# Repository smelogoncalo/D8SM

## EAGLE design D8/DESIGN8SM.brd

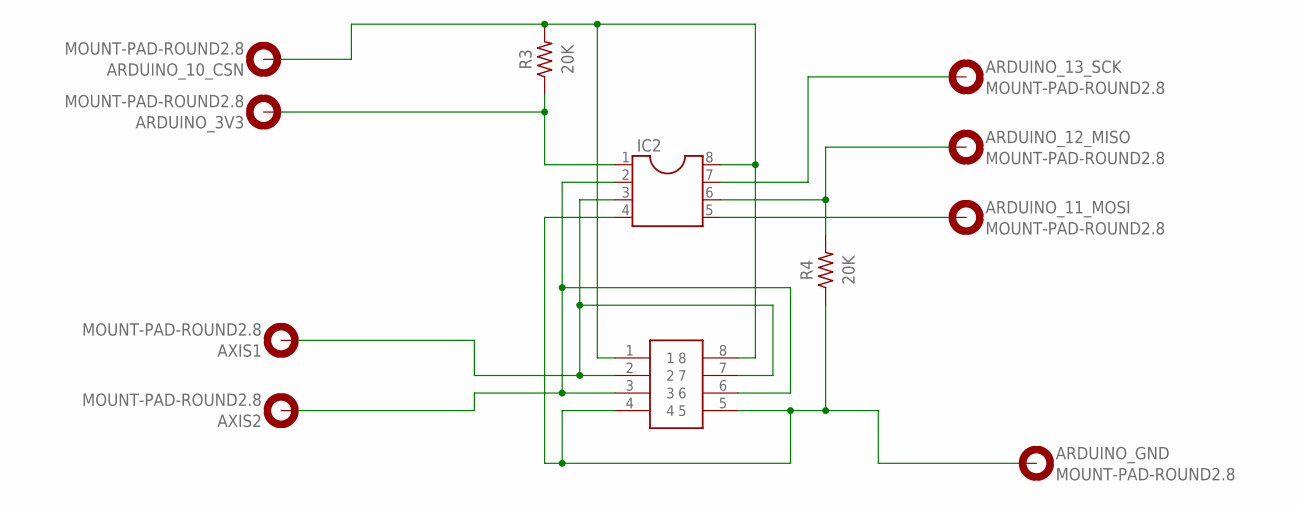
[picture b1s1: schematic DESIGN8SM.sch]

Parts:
ARDUINO_3V3, ARDUINO_10_CSN, ARDUINO_11_MOSI, ARDUINO_12_MISO, ARDUINO_13_SCK: MOUNT-PAD-ROUND2.8; 2,8-PAD
ARDUINO_GND: MOUNT-PAD-ROUND2.8; 2,8-PAD
AXIS1, AXIS2: MOUNT-PAD-ROUND2.8; 2,8-PAD
IC2: DIL8S; SOCKET-08
R3, R4: 20K; RESAD1176W63L850D250B
U$2: JOYSTICK

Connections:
unnamed: ARDUINO_GND.B2,8, IC2.4, R4.1, U$2.4, U$2.5
unnamed: AXIS1.B2,8, IC2.3, U$2.2, U$2.7
unnamed: AXIS2.B2,8, IC2.2, U$2.3, U$2.6
unnamed: ARDUINO_10_CSN.B2,8, IC2.8, R3.2, U$2.1, U$2.8
unnamed: ARDUINO_3V3.B2,8, IC2.1, R3.1
unnamed: ARDUINO_11_MOSI.B2,8, IC2.5
unnamed: ARDUINO_12_MISO.B2,8, IC2.6, R4.2
unnamed: ARDUINO_13_SCK.B2,8, IC2.7

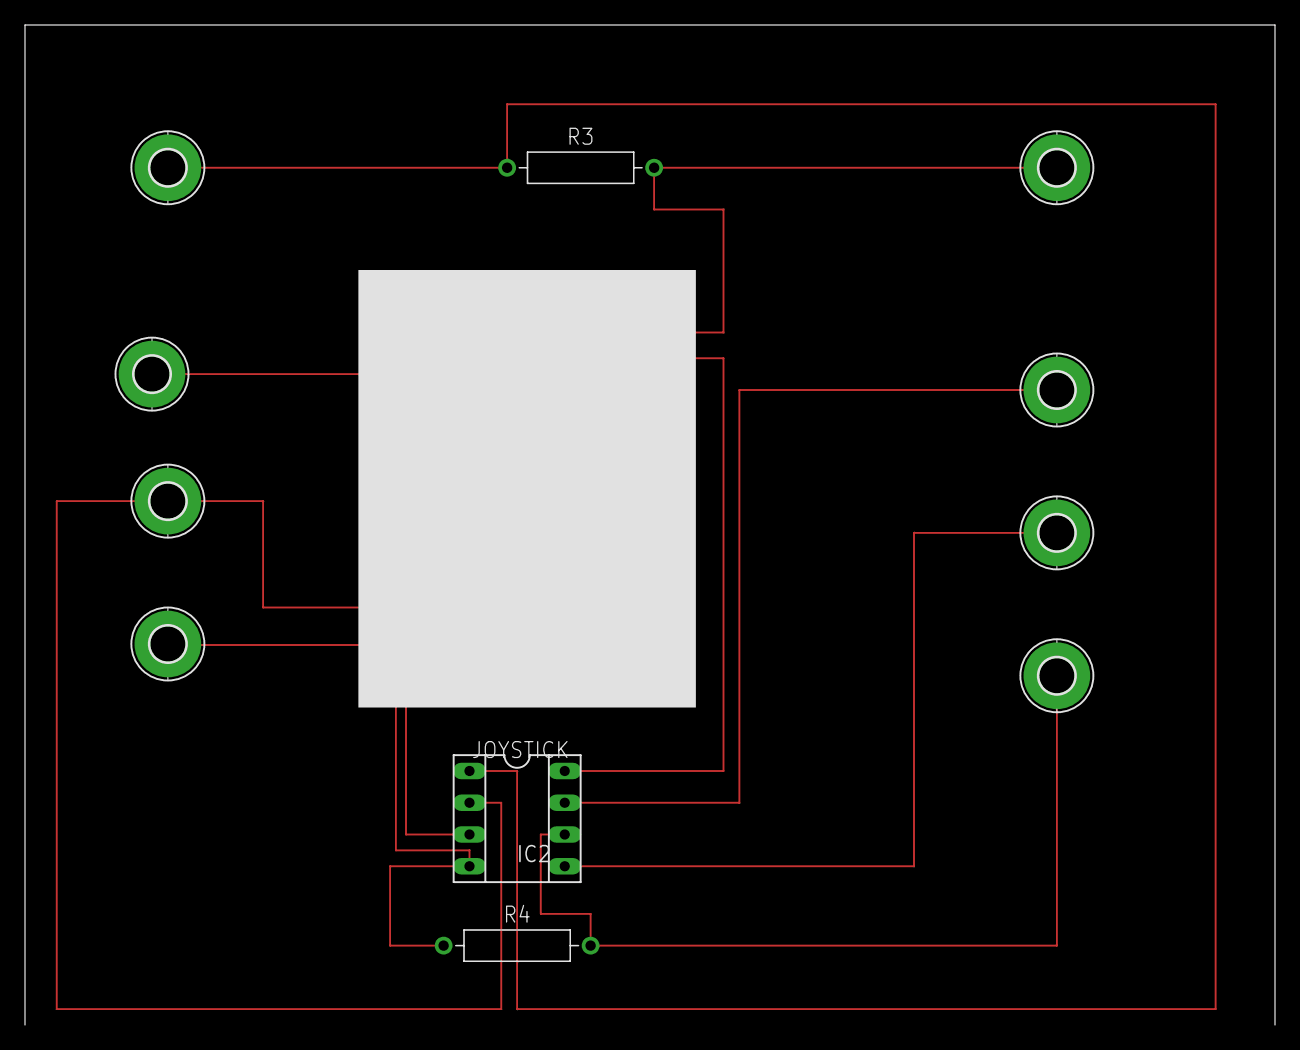
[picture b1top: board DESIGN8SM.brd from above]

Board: 2 copper layers, 100.0 x 80.0 mm, 12 parts (0 on the bottom side), 8 nets.
